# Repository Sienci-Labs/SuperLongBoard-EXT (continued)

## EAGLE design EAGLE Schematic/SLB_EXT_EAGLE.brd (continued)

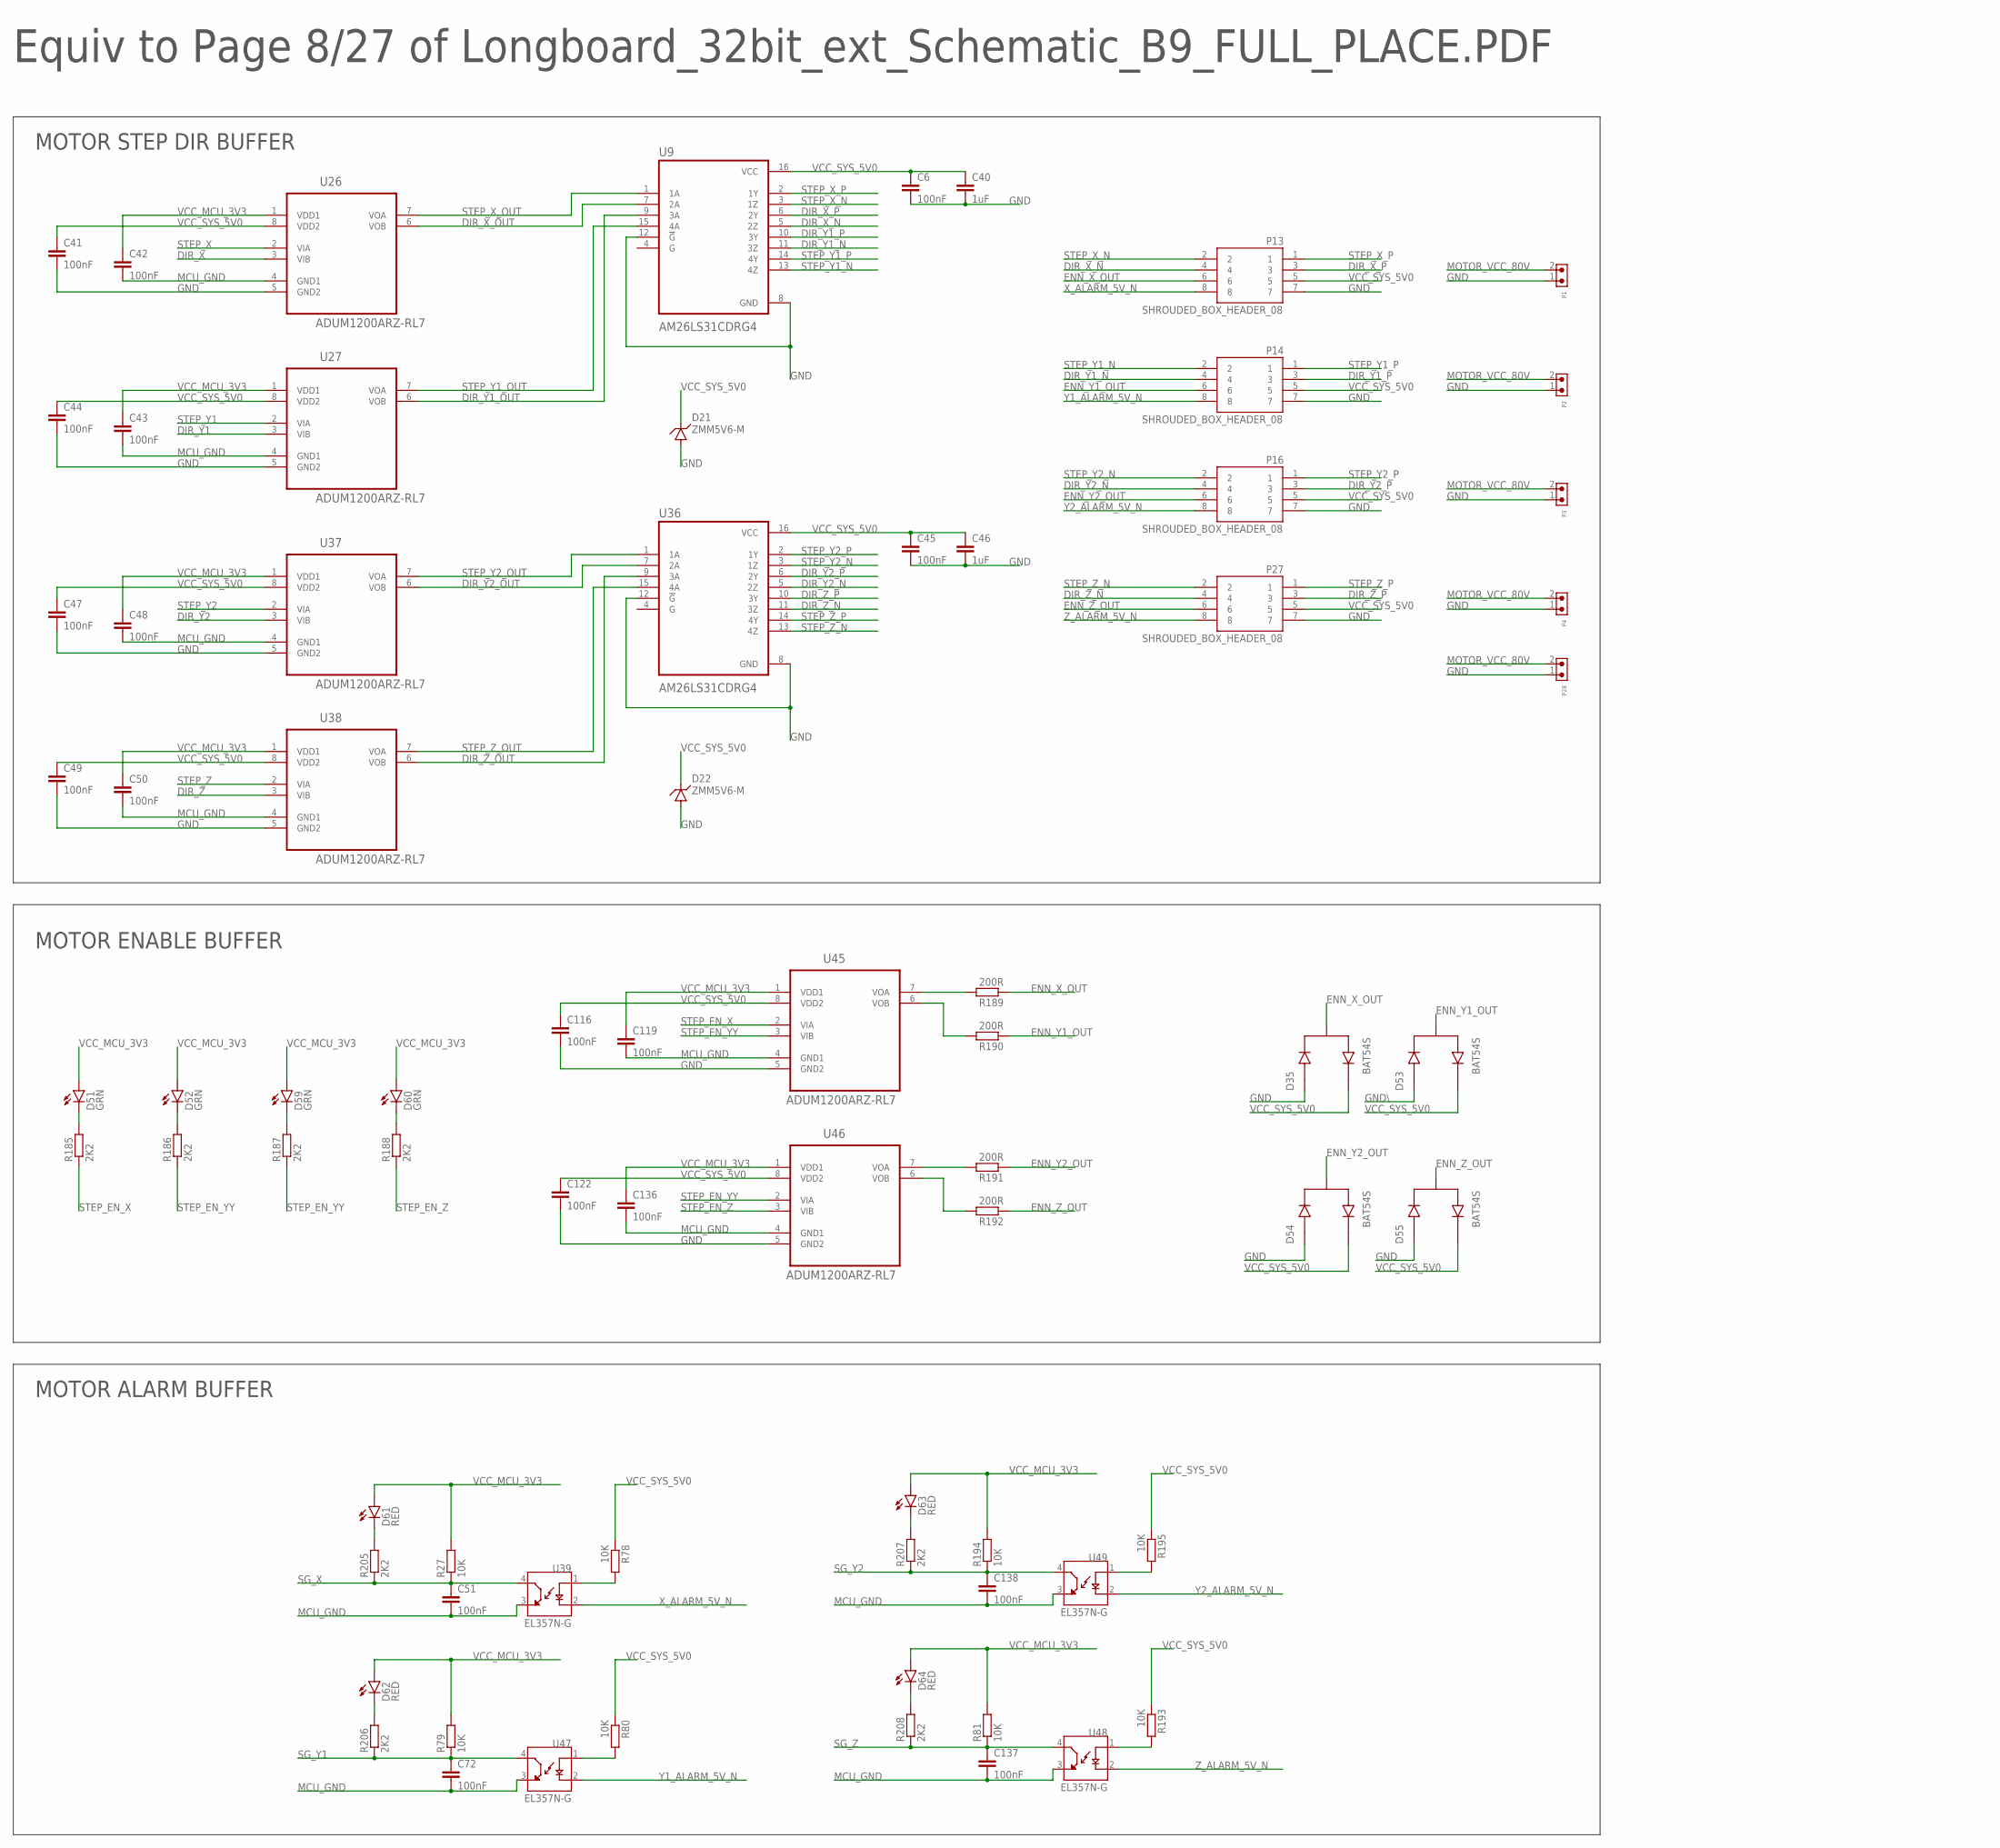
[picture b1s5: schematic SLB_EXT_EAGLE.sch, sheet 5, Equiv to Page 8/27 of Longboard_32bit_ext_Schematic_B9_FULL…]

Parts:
C6, C41, C42, C43, C44, C45, C47, C48, C49, C50, C51, C116, C119, C122, C136, C137, C138: 100nF; C0603K
C40, C46: 1uF; C0603K
C72: 100nF; C0402
D21, D22: ZMM5V6-M; MINIMELF
D35, D53, D54, D55: BAT54S; SOT95P240X120-3N
D51, D52, D59, D60: GRN; CHIP-LED0603
D61, D62, D63, D64: RED; CHIP-LED0603
P1, P2, P3, P4, P28: DB2EVC-3.81-2P-GN
P13, P14, P16, P27: SHROUDED_BOX_HEADER_08
R27, R79, R81, R194: 10K; R0402
R78, R80, R193, R195: 10K; R0603
R185, R186, R187, R188, R205, R206, R207, R208: 2K2; R0402
R189, R190, R191, R192: 200R; R0603
U9, U36: AM26LS31CDRG4; SOIC127P600X175-16N
U26, U27, U37, U38, U45, U46: ADUM1200ARZ-RL7; SOIC127P600X175-8N
U39, U47, U48, U49: EL357N-G; OPTO_EL357N-G

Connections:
DIR_X: U26.3 (VIB); also elsewhere on the board
DIR_X_N: P13.4, U9.5 (2Z)
DIR_X_OUT: U9.7 (2A), U26.6 (VOB)
DIR_X_P: P13.3, U9.6 (2Y)
DIR_Y1: U27.3 (VIB); also elsewhere on the board
DIR_Y1_N: P14.4, U9.11 (3Z)
DIR_Y1_OUT: U9.9 (3A), U27.6 (VOB)
DIR_Y1_P: P14.3, U9.10 (3Y)
DIR_Y2: U37.3 (VIB); also elsewhere on the board
DIR_Y2_N: P16.4, U36.5 (2Z)
DIR_Y2_OUT: U36.7 (2A), U37.6 (VOB)
DIR_Y2_P: P16.3, U36.6 (2Y)
DIR_Z: U38.3 (VIB); also elsewhere on the board
DIR_Z_N: P27.4, U36.11 (3Z)
DIR_Z_OUT: U36.9 (3A), U38.6 (VOB)
DIR_Z_P: P27.3, U36.10 (3Y)
ENN_X_OUT: D35.3, P13.6, R189.1
ENN_Y1_OUT: D53.3, P14.6, R190.1
ENN_Y2_OUT: D54.3, P16.6, R191.1
ENN_Z_OUT: D55.3, P27.6, R192.1
GND: C6.2, C40.2, C41.2, C44.2, C45.2, C46.2, C47.2, C49.2, C116.2, C122.2, D21.A, D22.A, D35.1, D54.1, D55.1, P1.1, P2.1, P3.1, P4.1, P13.7, P14.7, P16.7, P27.7, P28.1, U9.8 (GND), U9.12 (!G), U26.5 (GND2), U27.5 (GND2), U36.8 (GND), U36.12 (!G), U37.5 (GND2), U38.5 (GND2), U45.5 (GND2), U46.5 (GND2); also elsewhere on the board
GND\: D53.1
MCU_GND: C42.2, C43.2, C48.2, C50.2, C51.2, C72.2, C119.2, C136.2, C137.2, C138.2, U26.4 (GND1), U27.4 (GND1), U37.4 (GND1), U38.4 (GND1), U39.3 (ET), U45.4 (GND1), U46.4 (GND1), U47.3 (ET), U48.3 (ET), U49.3 (ET); also elsewhere on the board
MOTOR_VCC_80V: P1.2, P2.2, P3.2, P4.2, P28.2; also elsewhere on the board
unnamed: R189.2, U45.7 (VOA)
unnamed: R190.2, U45.6 (VOB)
unnamed: R191.2, U46.7 (VOA)
unnamed: R192.2, U46.6 (VOB)
unnamed: R78.2, U39.1 (A)
unnamed: D62.C, R206.2
unnamed: D61.C, R205.2
unnamed: R80.2, U47.1 (A)
unnamed: D63.C, R207.2
unnamed: R195.2, U49.1 (A)
unnamed: D64.C, R208.2
unnamed: R193.2, U48.1 (A)
unnamed: D51.C, R185.2
unnamed: D52.C, R186.2
unnamed: D59.C, R187.2
unnamed: D60.C, R188.2
SG_X: C51.1, R27.1, R205.1, U39.4 (CT); also elsewhere on the board
SG_Y1: C72.1, R79.1, R206.1, U47.4 (CT); also elsewhere on the board
SG_Y2: C138.1, R194.1, R207.1, U49.4 (CT); also elsewhere on the board
SG_Z: C137.1, R81.1, R208.1, U48.4 (CT); also elsewhere on the board
STEP_EN_X: R185.1, U45.2 (VIA); also elsewhere on the board
STEP_EN_YY: R186.1, R187.1, U45.3 (VIB), U46.2 (VIA); also elsewhere on the board
STEP_EN_Z: R188.1, U46.3 (VIB); also elsewhere on the board
STEP_X: U26.2 (VIA); also elsewhere on the board
STEP_X_N: P13.2, U9.3 (1Z)
STEP_X_OUT: U9.1 (1A), U26.7 (VOA)
STEP_X_P: P13.1, U9.2 (1Y)
STEP_Y1: U27.2 (VIA); also elsewhere on the board
STEP_Y1_N: P14.2, U9.13 (4Z)
STEP_Y1_OUT: U9.15 (4A), U27.7 (VOA)
STEP_Y1_P: P14.1, U9.14 (4Y)
STEP_Y2: U37.2 (VIA); also elsewhere on the board
STEP_Y2_N: P16.2, U36.3 (1Z)
STEP_Y2_OUT: U36.1 (1A), U37.7 (VOA)
STEP_Y2_P: P16.1, U36.2 (1Y)
STEP_Z: U38.2 (VIA); also elsewhere on the board
STEP_Z_N: P27.2, U36.13 (4Z)
STEP_Z_OUT: U36.15 (4A), U38.7 (VOA)
STEP_Z_P: P27.1, U36.14 (4Y)
VCC_MCU_3V3: C42.1, C43.1, C48.1, C50.1, C119.1, C136.1, D51.A, D52.A, D59.A, D60.A, D61.A, D62.A, D63.A, D64.A, R27.2, R79.2, R81.2, R194.2, U26.1 (VDD1), U27.1 (VDD1), U37.1 (VDD1), U38.1 (VDD1), U45.1 (VDD1), U46.1 (VDD1); also elsewhere on the board
VCC_SYS_5V0: C6.1, C40.1, C41.1, C44.1, C45.1, C46.1, C47.1, C49.1, C116.1, C122.1, D21.C, D22.C, D35.2, D53.2, D54.2, D55.2, P13.5, P14.5, P16.5, P27.5, R78.1, R80.1, R193.1, R195.1, U9.16 (VCC), U26.8 (VDD2), U27.8 (VDD2), U36.16 (VCC), U37.8 (VDD2), U38.8 (VDD2), U45.8 (VDD2), U46.8 (VDD2); also elsewhere on the board
X_ALARM_5V_N: P13.8, U39.2 (C)
Y1_ALARM_5V_N: P14.8, U47.2 (C)
Y2_ALARM_5V_N: P16.8, U49.2 (C)
Z_ALARM_5V_N: P27.8, U48.2 (C)

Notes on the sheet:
Equiv to Page 8/27 of Longboard_32bit_ext_Schematic_B9_FULL_PLACE.PDF
MOTOR STEP DIR BUFFER
MOTOR ENABLE BUFFER
MOTOR ALARM BUFFER

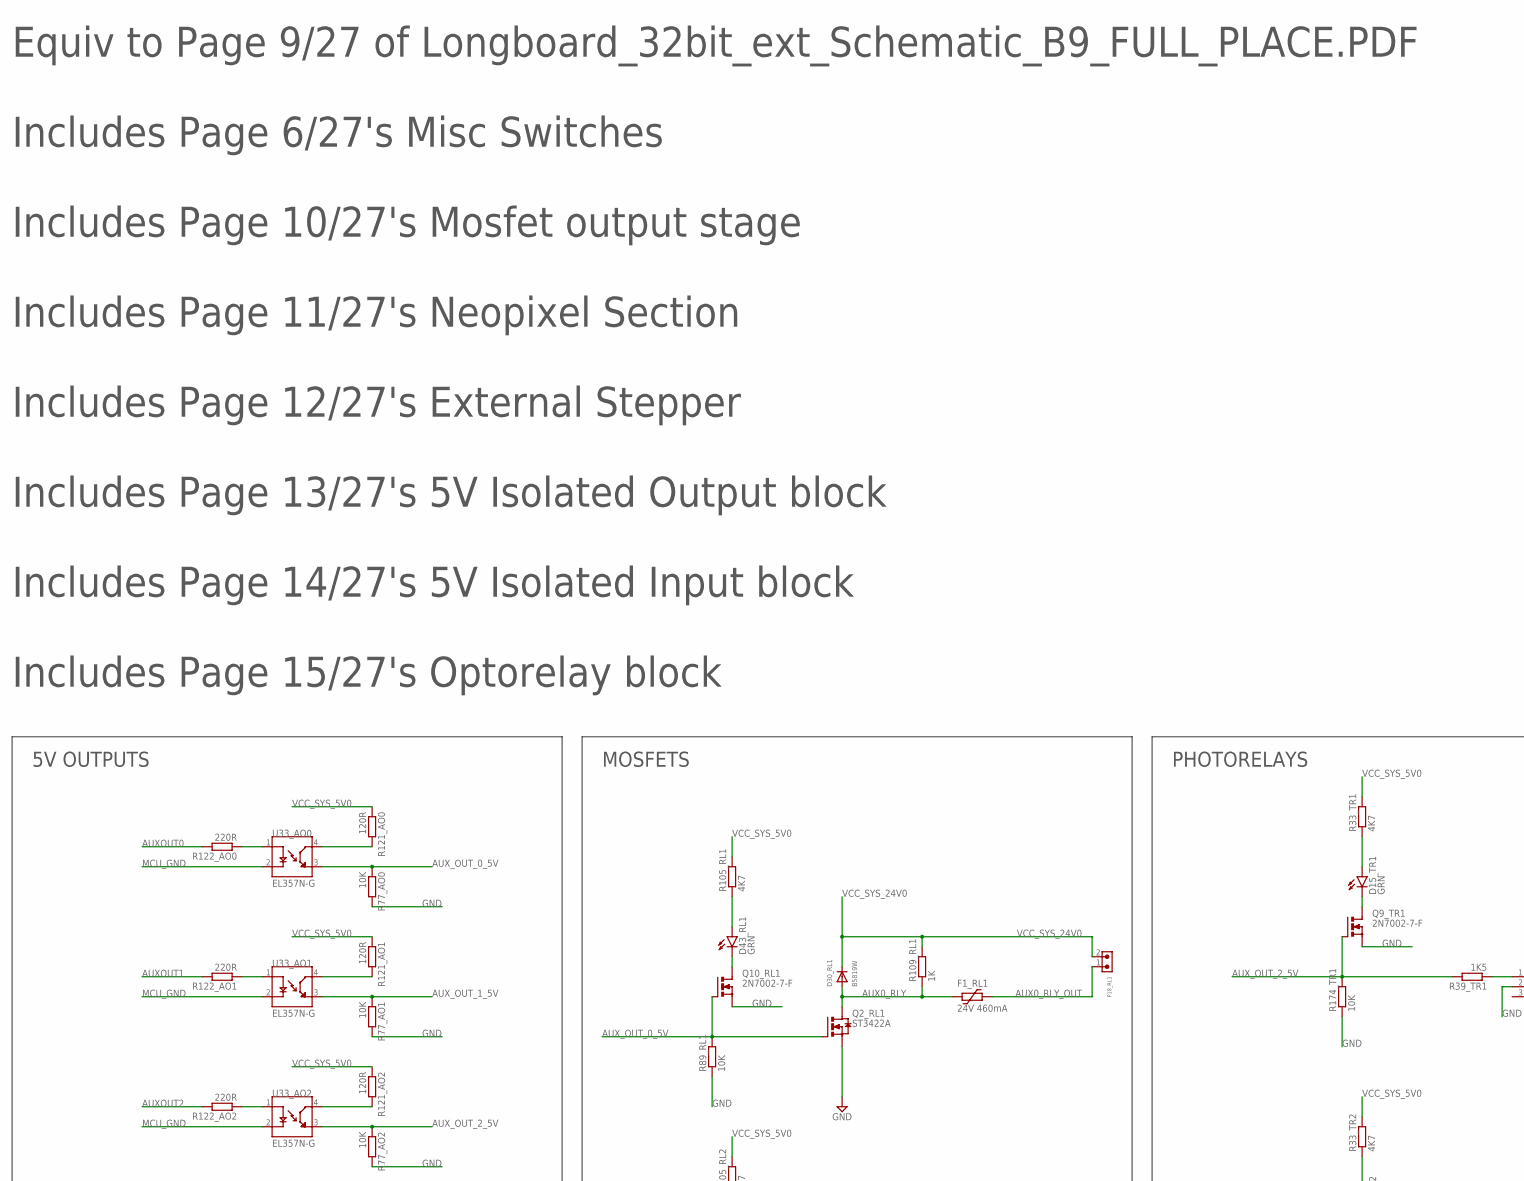
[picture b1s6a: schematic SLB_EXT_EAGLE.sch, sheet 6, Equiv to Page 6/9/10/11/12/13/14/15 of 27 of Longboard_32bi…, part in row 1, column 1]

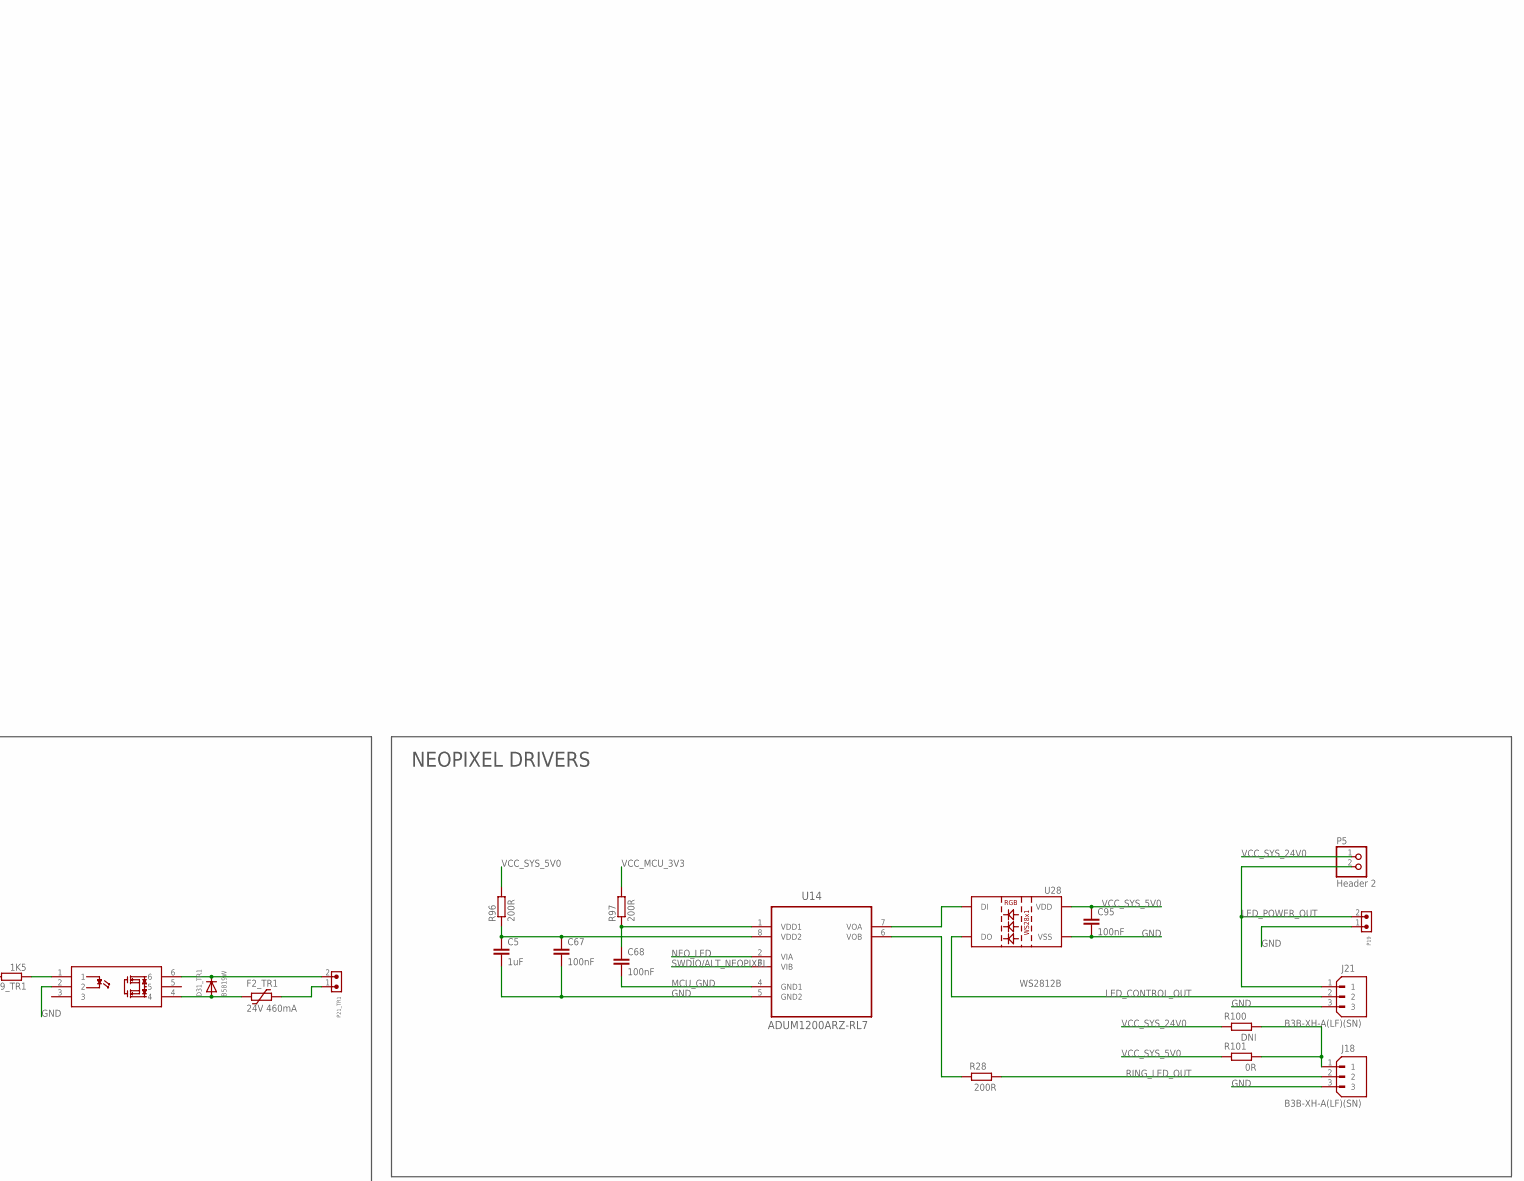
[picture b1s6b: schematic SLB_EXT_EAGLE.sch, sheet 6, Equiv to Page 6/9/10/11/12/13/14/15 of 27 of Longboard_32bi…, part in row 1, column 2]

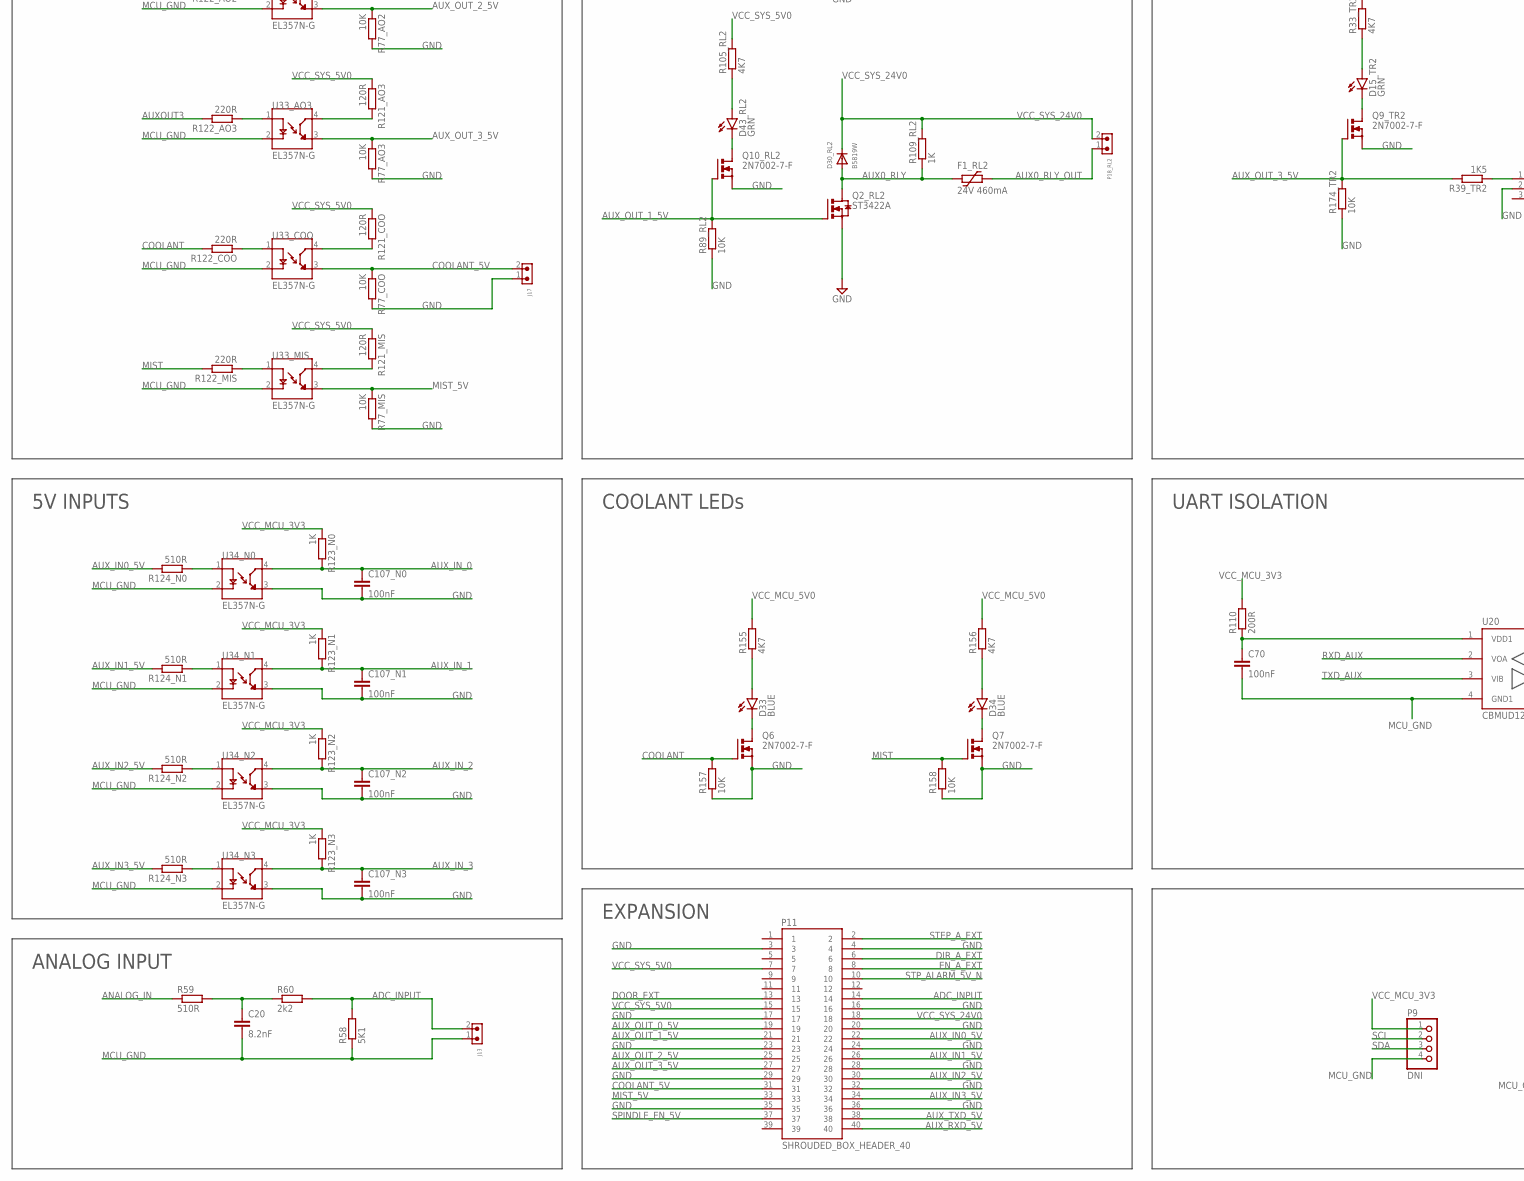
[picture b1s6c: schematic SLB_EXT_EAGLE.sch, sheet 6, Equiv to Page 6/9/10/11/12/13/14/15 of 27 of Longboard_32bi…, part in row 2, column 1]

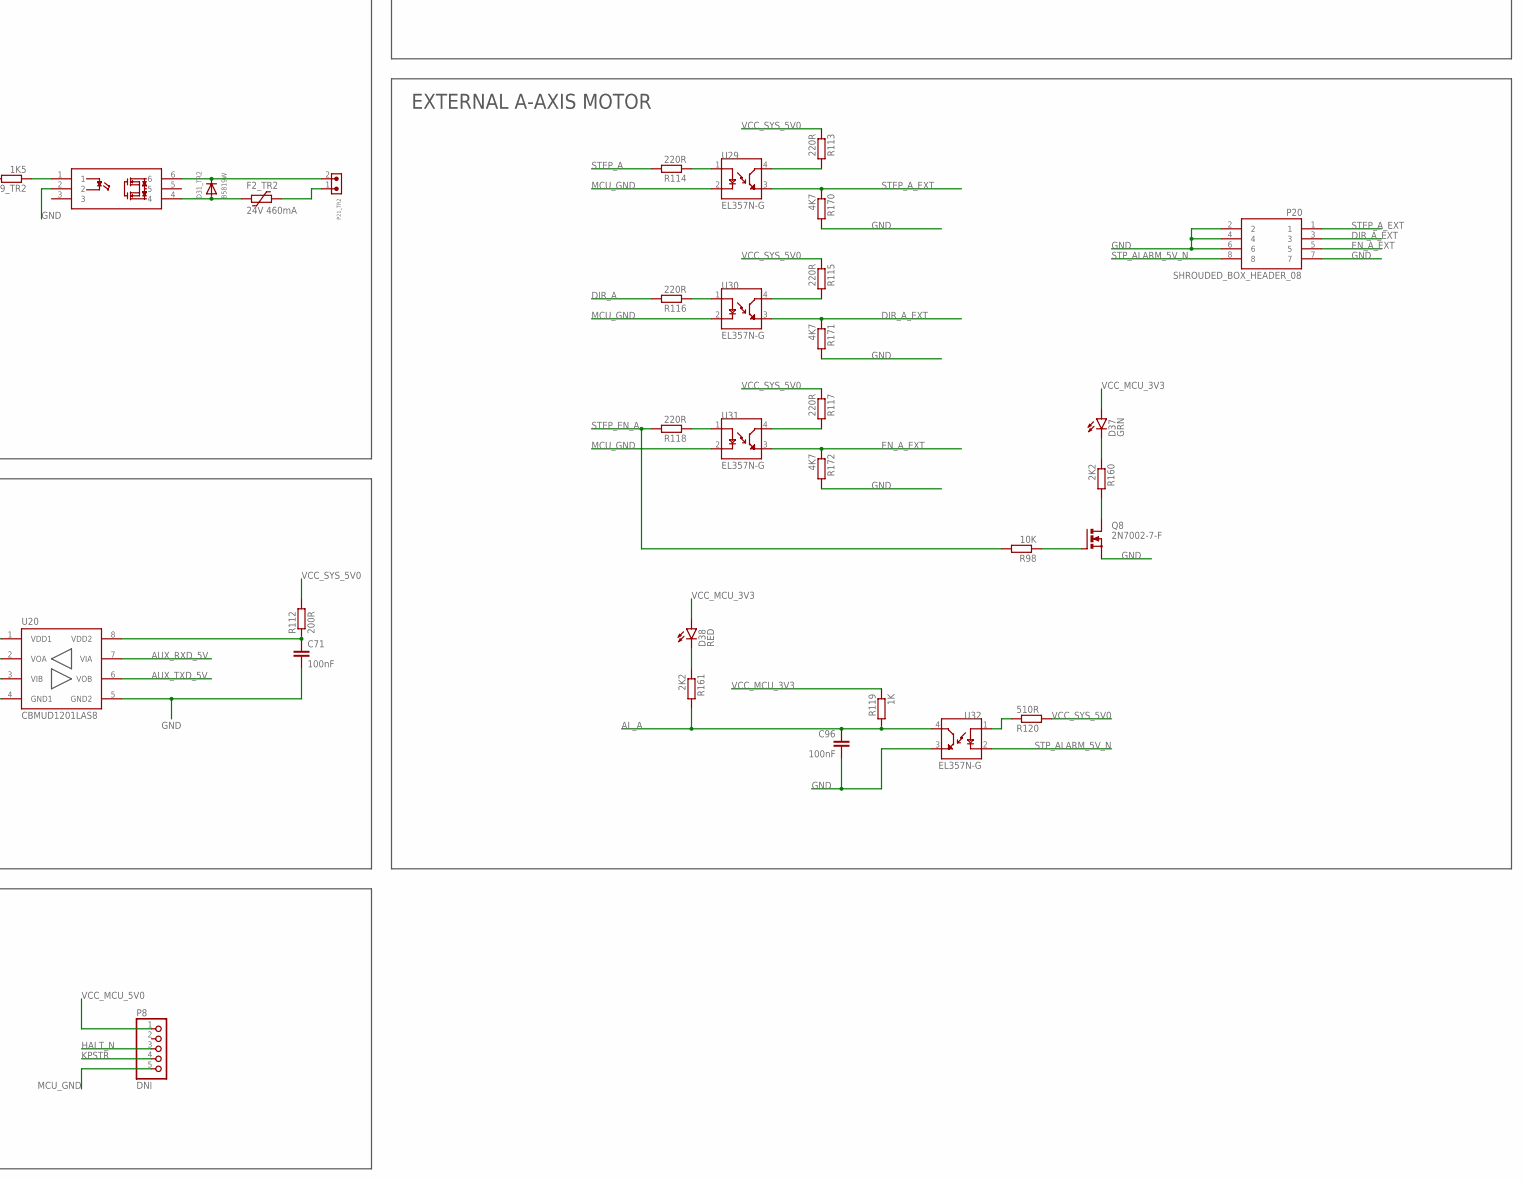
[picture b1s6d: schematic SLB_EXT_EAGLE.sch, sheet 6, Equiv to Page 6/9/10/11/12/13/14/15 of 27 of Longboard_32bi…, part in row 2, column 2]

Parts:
C5: 1uF; C0603K
C20: 8.2nF; C0603K
C67, C68, C95: 100nF; C0603K
C70, C71, C96, C107_N0, C107_N1, C107_N2, C107_N3: 100nF; C0402
D15_TR1, D15_TR2, D37, D43_RL1, D43_RL2: GRN; CHIP-LED0603
D30_RL1, D30_RL2, D31_TR1, D31_TR2: B5819W; SOD123FL
D33, D34: BLUE; CHIP-LED0603
D38: RED; CHIP-LED0603
F1_RL1, F1_RL2, F2_TR1, F2_TR2: 24V 460mA; 1206L
J13, J17: WJ15EDGK-3.81-2P; DB2EVC-3.81-2P-GN
J18, J21: B3B-XH-A(LF)(SN); JST_B3B-XH-A(LF)(SN)
K1_TR1, K1_TR2: TLP3109A
P5: Header 2; 1X02
P8: DNI; 1X05
P9: DNI; 1X04
P11: SHROUDED_BOX_HEADER_40
P18_RL1, P18_RL2, P19, P21_TR1, P21_TR2: WJ15EDGK-3.81-2P; DB2EVC-3.81-2P-GN
P20: SHROUDED_BOX_HEADER_08
Q2_RL1, Q2_RL2: ST3422A; SOT-23
Q6, Q7, Q8, Q9_TR1, Q9_TR2, Q10_RL1, Q10_RL2: 2N7002-7-F; SOT-23
R28, R96, R110, R112: 200R; R0402
R33_TR1, R33_TR2, R105_RL1, R105_RL2, R155, R156, R170, R171, R172: 4K7; R0402
R39_TR1, R39_TR2: 1K5; R0402
R58: 5K1; R0402
R59, R120, R124_N0, R124_N1, R124_N2, R124_N3: 510R; R0402
R60: 2k2; R0402
R77_AO0, R77_AO1, R77_AO2, R77_AO3, R77_COO, R77_MIS, R89_RL1, R89_RL2, R174_TR1, R174_TR2: 10K; R0402
R97: 200R; R0603
R98, R157, R158: 10K; R0603
R100: DNI; R0402
R101: 0R; R0402
R109_RL1, R109_RL2: 1K; R0603
R113, R114, R115, R117, R118, R122_AO0, R122_AO1, R122_AO2, R122_AO3, R122_COO, R122_MIS: 220R; R0402
R116: 220R; R0603
R119, R123_N0, R123_N1, R123_N2, R123_N3: 1K; R0402
R121_AO0, R121_AO1, R121_AO2, R121_AO3, R121_COO, R121_MIS: 120R; R0402
R160, R161: 2K2; R0402
U14: ADUM1200ARZ-RL7; SOIC127P600X175-8N
U20: CBMUD1201LAS8; SOIC-8
U28: WS2812B
U29, U30, U31, U32, U33_AO0, U33_AO1, U33_AO2, U33_AO3, U33_COO, U33_MIS, U34_N0, U34_N1, U34_N2, U34_N3: EL357N-G; OPTO_EL357N-G

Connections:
ADC_INPUT: J13.2, P11.14, R58.2, R60.2
AL_A: C96.1, R119.2, R161.2, U32.4 (CT); also elsewhere on the board
ANALOG_IN: R59.1; also elsewhere on the board
AUX0_RLY: D30_RL1.A, D30_RL2.A, F1_RL1.2, F1_RL2.2, Q2_RL1.P3 (D), Q2_RL2.P3 (D), R109_RL1.1, R109_RL2.1
AUX0_RLY_OUT: F1_RL1.1, F1_RL2.1, P18_RL1.1, P18_RL2.1
AUXOUT0: R122_AO0.2; also elsewhere on the board
AUXOUT1: R122_AO1.2; also elsewhere on the board
AUXOUT2: R122_AO2.2; also elsewhere on the board
AUXOUT3: R122_AO3.2; also elsewhere on the board
AUX_IN0_5V: P11.22, R124_N0.2
AUX_IN1_5V: P11.26, R124_N1.2
AUX_IN2_5V: P11.30, R124_N2.2
AUX_IN3_5V: P11.34, R124_N3.2
AUX_IN_0: C107_N0.1, R123_N0.2, U34_N0.4 (CT); also elsewhere on the board
AUX_IN_1: C107_N1.1, R123_N1.2, U34_N1.4 (CT); also elsewhere on the board
AUX_IN_2: C107_N2.1, R123_N2.2, U34_N2.4 (CT); also elsewhere on the board
AUX_IN_3: C107_N3.1, R123_N3.2, U34_N3.4 (CT); also elsewhere on the board
AUX_OUT_0_5V: P11.19, Q2_RL1.P1 (G), Q10_RL1.P1 (G), R77_AO0.1, R89_RL1.2, U33_AO0.3 (ET)
AUX_OUT_1_5V: P11.21, Q2_RL2.P1 (G), Q10_RL2.P1 (G), R77_AO1.1, R89_RL2.2, U33_AO1.3 (ET)
AUX_OUT_2_5V: P11.25, Q9_TR1.P1 (G), R39_TR1.2, R77_AO2.1, R174_TR1.2, U33_AO2.3 (ET)
AUX_OUT_3_5V: P11.27, Q9_TR2.P1 (G), R39_TR2.2, R77_AO3.1, R174_TR2.2, U33_AO3.3 (ET)
AUX_RXD_5V: P11.40, U20.7 (VIA)
AUX_TXD_5V: P11.38, U20.6 (VOB)
COOLANT: Q6.P1 (G), R122_COO.2, R157.2; also elsewhere on the board
COOLANT_5V: J17.2, P11.31, R77_COO.1, U33_COO.3 (ET)
DIR_A: R116.2; also elsewhere on the board
DIR_A_EXT: P11.6, P20.3, R171.1, U30.3 (ET)
DOOR_EXT: P11.13; also elsewhere on the board
EN_A_EXT: P11.8, P20.5, R172.1, U31.3 (ET)
GND: C5.2, C67.2, C71.2, C95.2, C96.2, C107_N0.2, C107_N1.2, C107_N2.2, C107_N3.2, J17.1, J18.3, J21.3, K1_TR1.2, K1_TR2.2, P11.3, P11.4, P11.16, P11.17, P11.20, P11.23, P11.24, P11.28, P11.29, P11.32, P11.35, P11.36, P19.1, P20.2, P20.4, P20.6, P20.7, Q2_RL1.P2 (S), Q2_RL2.P2 (S), Q6.P2 (S), Q7.P2 (S), Q8.P2 (S), Q9_TR1.P2 (S), Q9_TR2.P2 (S), Q10_RL1.P2 (S), Q10_RL2.P2 (S), R77_AO0.2, R77_AO1.2, R77_AO2.2, R77_AO3.2, R77_COO.2, R77_MIS.2, R89_RL1.1, R89_RL2.1, R157.1, R158.1, R170.2, R171.2, R172.2, R174_TR1.1, R174_TR2.1, U14.5 (GND2), U20.5 (GND2), U28.3 (VSS), U32.3 (ET), U34_N0.3 (ET), U34_N1.3 (ET), U34_N2.3 (ET), U34_N3.3 (ET); also elsewhere on the board
HALT_N: P8.3; also elsewhere on the board
KPSTR: P8.4; also elsewhere on the board
LED_CONTROL_OUT: J21.2, U28.2 (DO)
LED_POWER_OUT: J21.1, P5.2, P19.2
MCU_GND: C20.2, C68.2, C70.2, J13.1, P8.5, P9.4, R58.1, U14.4 (GND1), U20.4 (GND1), U29.2 (C), U30.2 (C), U31.2 (C), U33_AO0.2 (C), U33_AO1.2 (C), U33_AO2.2 (C), U33_AO3.2 (C), U33_COO.2 (C), U33_MIS.2 (C), U34_N0.2 (C), U34_N1.2 (C), U34_N2.2 (C), U34_N3.2 (C); also elsewhere on the board
MIST: Q7.P1 (G), R122_MIS.2, R158.2; also elsewhere on the board
MIST_5V: P11.33, R77_MIS.1, U33_MIS.3 (ET)
unnamed: R122_AO0.1, U33_AO0.1 (A)
unnamed: D43_RL1.A, R105_RL1.1
unnamed: R122_MIS.1, U33_MIS.1 (A)
unnamed: R121_AO0.2, U33_AO0.4 (CT)
unnamed: R122_AO1.1, U33_AO1.1 (A)
unnamed: D43_RL1.C, Q10_RL1.P3 (D)
unnamed: D15_TR1.A, R33_TR1.1
unnamed: R121_AO1.2, U33_AO1.4 (CT)
unnamed: R122_AO2.1, U33_AO2.1 (A)
unnamed: D43_RL2.A, R105_RL2.1
unnamed: D43_RL2.C, Q10_RL2.P3 (D)
unnamed: R121_AO2.2, U33_AO2.4 (CT)
unnamed: R122_AO3.1, U33_AO3.1 (A)
unnamed: R121_MIS.2, U33_MIS.4 (CT)
unnamed: D15_TR1.C, Q9_TR1.P3 (D)
unnamed: R121_AO3.2, U33_AO3.4 (CT)
unnamed: R122_COO.1, U33_COO.1 (A)
unnamed: K1_TR1.1, R39_TR1.1
unnamed: D31_TR1.C, K1_TR1.6, P21_TR1.2
unnamed: R121_COO.2, U33_COO.4 (CT)
unnamed: D31_TR1.A, F2_TR1.2, K1_TR1.4
unnamed: F2_TR1.1, P21_TR1.1
unnamed: D15_TR2.A, R33_TR2.1
unnamed: D15_TR2.C, Q9_TR2.P3 (D)
unnamed: K1_TR2.1, R39_TR2.1
unnamed: D31_TR2.C, K1_TR2.6, P21_TR2.2
unnamed: D31_TR2.A, F2_TR2.2, K1_TR2.4
unnamed: F2_TR2.1, P21_TR2.1
unnamed: R124_N0.1, U34_N0.1 (A)
unnamed: R124_N1.1, U34_N1.1 (A)
unnamed: R124_N2.1, U34_N2.1 (A)
unnamed: R120.1, U32.1 (A)
unnamed: D33.A, R155.1
unnamed: D33.C, Q6.P3 (D)
unnamed: D34.A, R156.1
unnamed: D34.C, Q7.P3 (D)
unnamed: C5.1, C67.1, R96.1, U14.8 (VDD2)
unnamed: C68.1, R97.1, U14.1 (VDD1)
unnamed: C70.1, R110.1, U20.1 (VDD1)
unnamed: C71.1, R112.1, U20.8 (VDD2)
unnamed: R28.2, U14.6 (VOB)
unnamed: U14.7 (VOA), U28.4 (DI)
unnamed: R114.1, U29.1 (A)
unnamed: R113.2, U29.4 (CT)
unnamed: R116.1, U30.1 (A)
unnamed: R115.2, U30.4 (CT)
unnamed: R118.1, U31.1 (A)
unnamed: R117.2, U31.4 (CT)
unnamed: D37.C, R160.1
unnamed: Q8.P3 (D), R160.2
unnamed: Q8.P1 (G), R98.1
unnamed: D38.C, R161.1
unnamed: C20.1, R59.2, R60.1
unnamed: J18.1, R100.1, R101.1
unnamed: R124_N3.1, U34_N3.1 (A)
NEO_LED: U14.2 (VIA); also elsewhere on the board
RING_LED_OUT: J18.2, R28.1
RXD_AUX: U20.2 (VOA); also elsewhere on the board
SCL: P9.2; also elsewhere on the board
SDA: P9.3; also elsewhere on the board
SPINDLE_EN_5V: P11.37; also elsewhere on the board
STEP_A: R114.2; also elsewhere on the board
STEP_A_EXT: P11.2, P20.1, R170.1, U29.3 (ET)
STEP_EN_A: R98.2, R118.2; also elsewhere on the board
STP_ALARM_5V_N: P11.10, P20.8, U32.2 (C)
SWDIO/ALT_NEOPIXEL: U14.3 (VIB); also elsewhere on the board
TXD_AUX: U20.3 (VIB); also elsewhere on the board
VCC_MCU_3V3: D37.A, D38.A, P9.1, R97.2, R110.2, R119.1, R123_N0.1, R123_N1.1, R123_N2.1, R123_N3.1; also elsewhere on the board
VCC_MCU_5V0: P8.1, R155.2, R156.2; also elsewhere on the board
VCC_SYS_5V0: C95.1, P11.7, P11.15, R33_TR1.2, R33_TR2.2, R96.2, R101.2, R105_RL1.2, R105_RL2.2, R112.2, R113.1, R115.1, R117.1, R120.2, R121_AO0.1, R121_AO1.1, R121_AO2.1, R121_AO3.1, R121_COO.1, R121_MIS.1, U28.1 (VDD); also elsewhere on the board
VCC_SYS_24V0: D30_RL1.C, D30_RL2.C, P5.1, P11.18, P18_RL1.2, P18_RL2.2, R100.2, R109_RL1.2, R109_RL2.2; also elsewhere on the board

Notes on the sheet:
Equiv to Page 9/27 of Longboard_32bit_ext_Schematic_B9_FULL_PLACE.PDF Includes Page 6/27's Misc Switches Includes Page 10/27's Mosfet output stage Includes Page 11/27's Neopixel Section Includes Page 12/27's External Stepper Includes Page 13/27's 5V Isolated Output block Includes Page 14/27's 5V Is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
5V OUTPUTS
MOSFETS
PHOTORELAYS
5V INPUTS
COOLANT LEDs
UART ISOLATION
NEOPIXEL DRIVERS
EXTERNAL A-AXIS MOTOR
ANALOG INPUT
EXPANSION

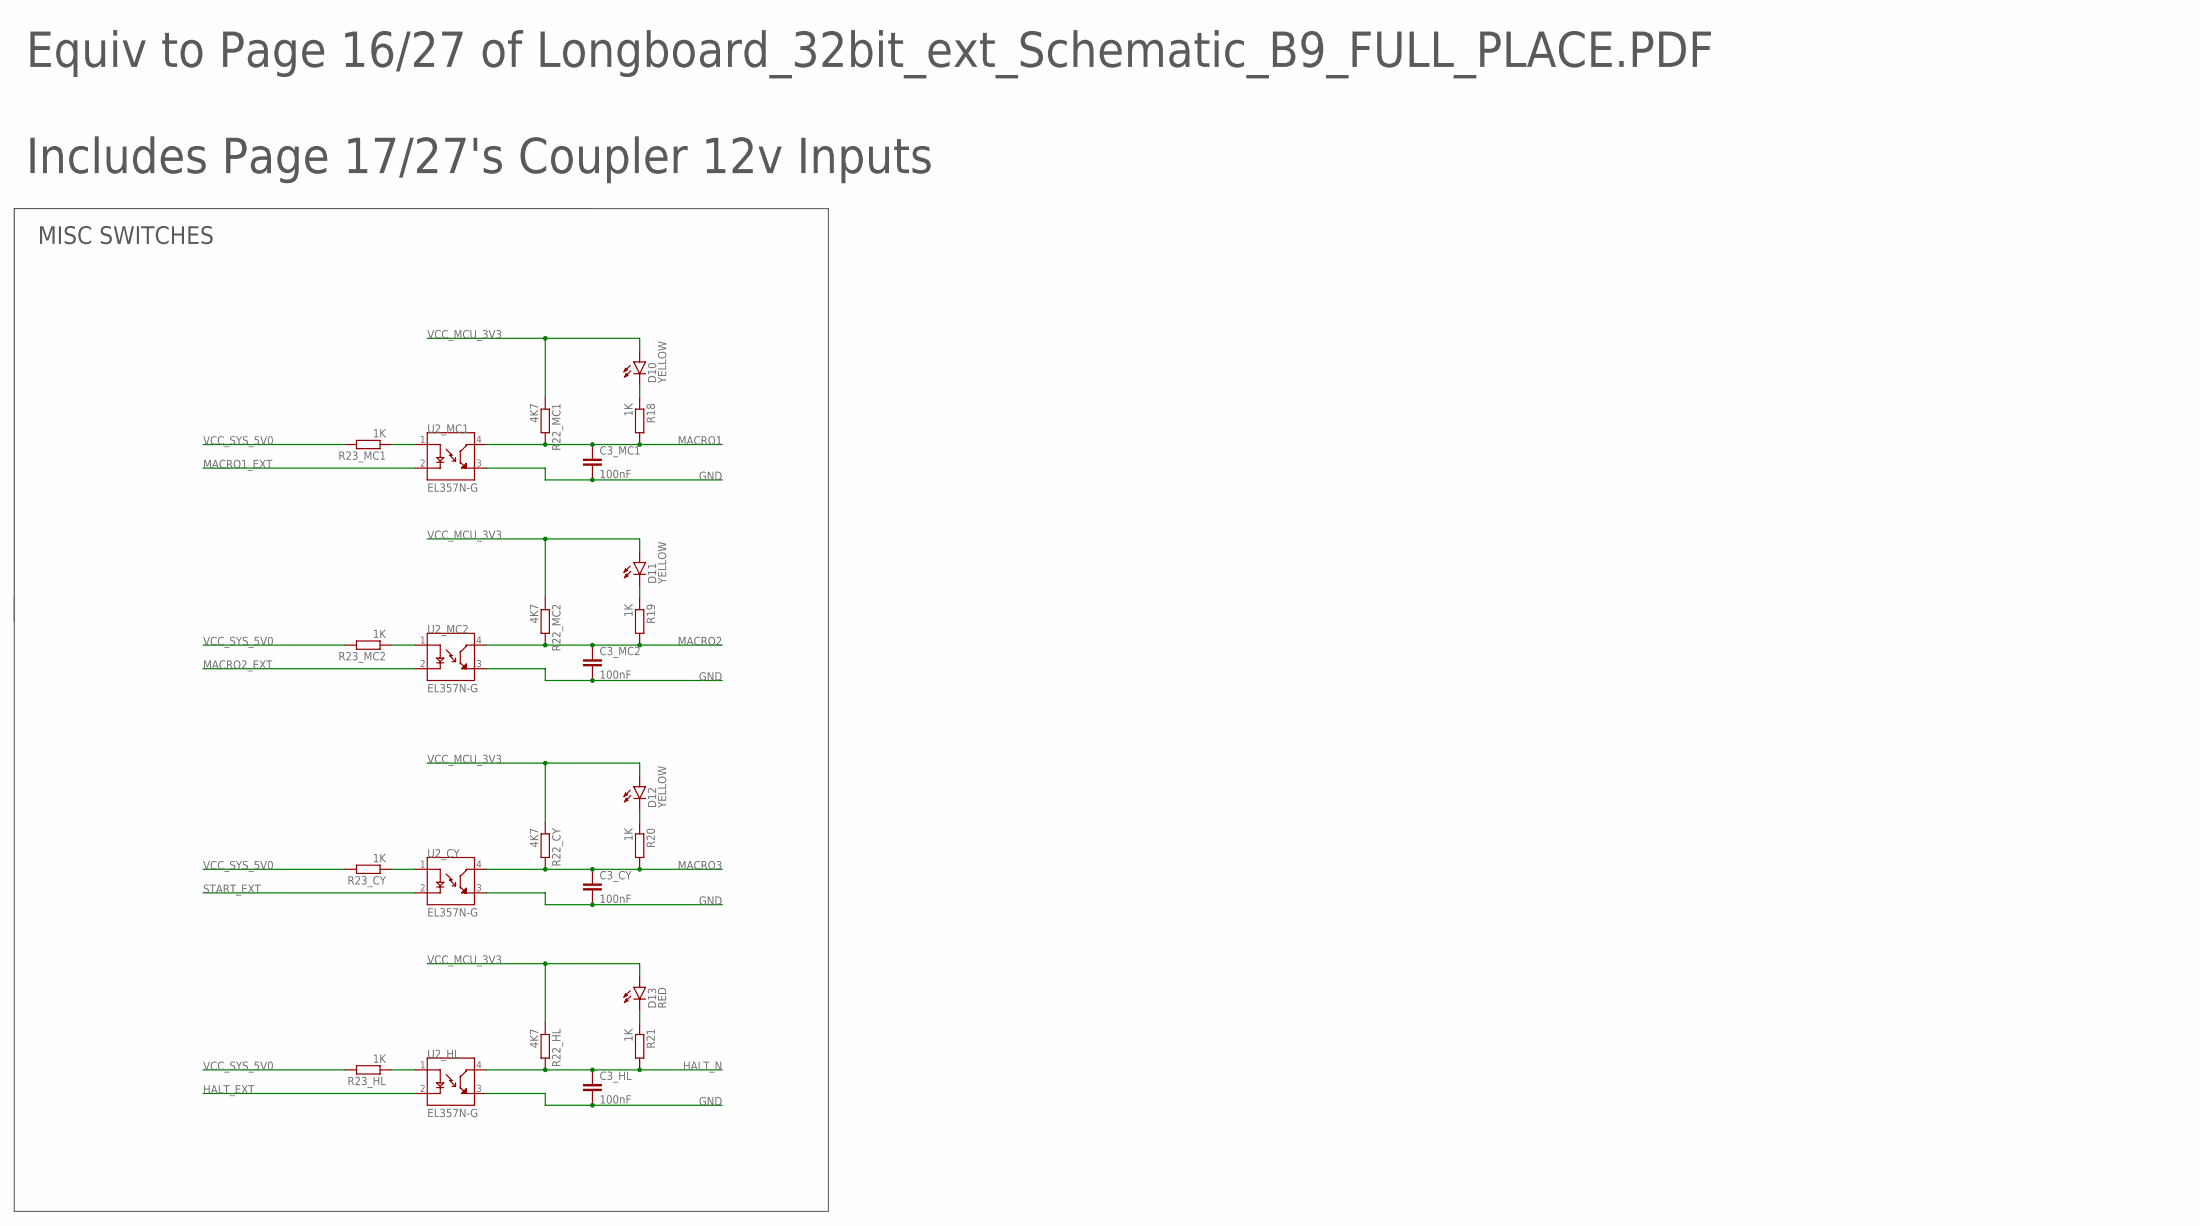
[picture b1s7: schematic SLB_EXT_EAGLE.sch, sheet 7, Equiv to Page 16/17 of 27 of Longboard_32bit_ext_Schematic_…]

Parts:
C3_CY: 100nF; C0603K
C3_HL, C3_MC1, C3_MC2: 100nF; C0402
D10, D11, D12: YELLOW; CHIP-LED0603
D13: RED; CHIP-LED0603
R18, R19, R20, R21: 1K; R0402
R22_CY: 4K7; R0603
R22_HL, R22_MC1, R22_MC2: 4K7; R0402
R23_CY, R23_HL, R23_MC1, R23_MC2: 1K; R0603
U2_CY, U2_HL, U2_MC1, U2_MC2: EL357N-G; OPTO_EL357N-G

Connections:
GND: C3_CY.2, C3_HL.2, C3_MC1.2, C3_MC2.2, U2_CY.3 (ET), U2_HL.3 (ET), U2_MC1.3 (ET), U2_MC2.3 (ET); also elsewhere on the board
HALT_EXT: U2_HL.2 (C); also elsewhere on the board
HALT_N: C3_HL.1, R21.2, R22_HL.2, U2_HL.4 (CT); also elsewhere on the board
MACRO1: C3_MC1.1, R18.2, R22_MC1.2, U2_MC1.4 (CT); also elsewhere on the board
MACRO1_EXT: U2_MC1.2 (C); also elsewhere on the board
MACRO2: C3_MC2.1, R19.2, R22_MC2.2, U2_MC2.4 (CT); also elsewhere on the board
MACRO2_EXT: U2_MC2.2 (C); also elsewhere on the board
MACRO3: C3_CY.1, R20.2, R22_CY.2, U2_CY.4 (CT); also elsewhere on the board
unnamed: R23_MC1.1, U2_MC1.1 (A)
unnamed: D10.C, R18.1
unnamed: R23_MC2.1, U2_MC2.1 (A)
unnamed: D11.C, R19.1
unnamed: R23_CY.1, U2_CY.1 (A)
unnamed: D12.C, R20.1
unnamed: R23_HL.1, U2_HL.1 (A)
unnamed: D13.C, R21.1
START_EXT: U2_CY.2 (C); also elsewhere on the board
VCC_MCU_3V3: D10.A, D11.A, D12.A, D13.A, R22_CY.1, R22_HL.1, R22_MC1.1, R22_MC2.1; also elsewhere on the board
VCC_SYS_5V0: R23_CY.2, R23_HL.2, R23_MC1.2, R23_MC2.2; also elsewhere on the board

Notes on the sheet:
Equiv to Page 16/27 of Longboard_32bit_ext_Schematic_B9_FULL_PLACE.PDF Includes Page 17/27's Coupler 12v Inputs
MISC SWITCHES
